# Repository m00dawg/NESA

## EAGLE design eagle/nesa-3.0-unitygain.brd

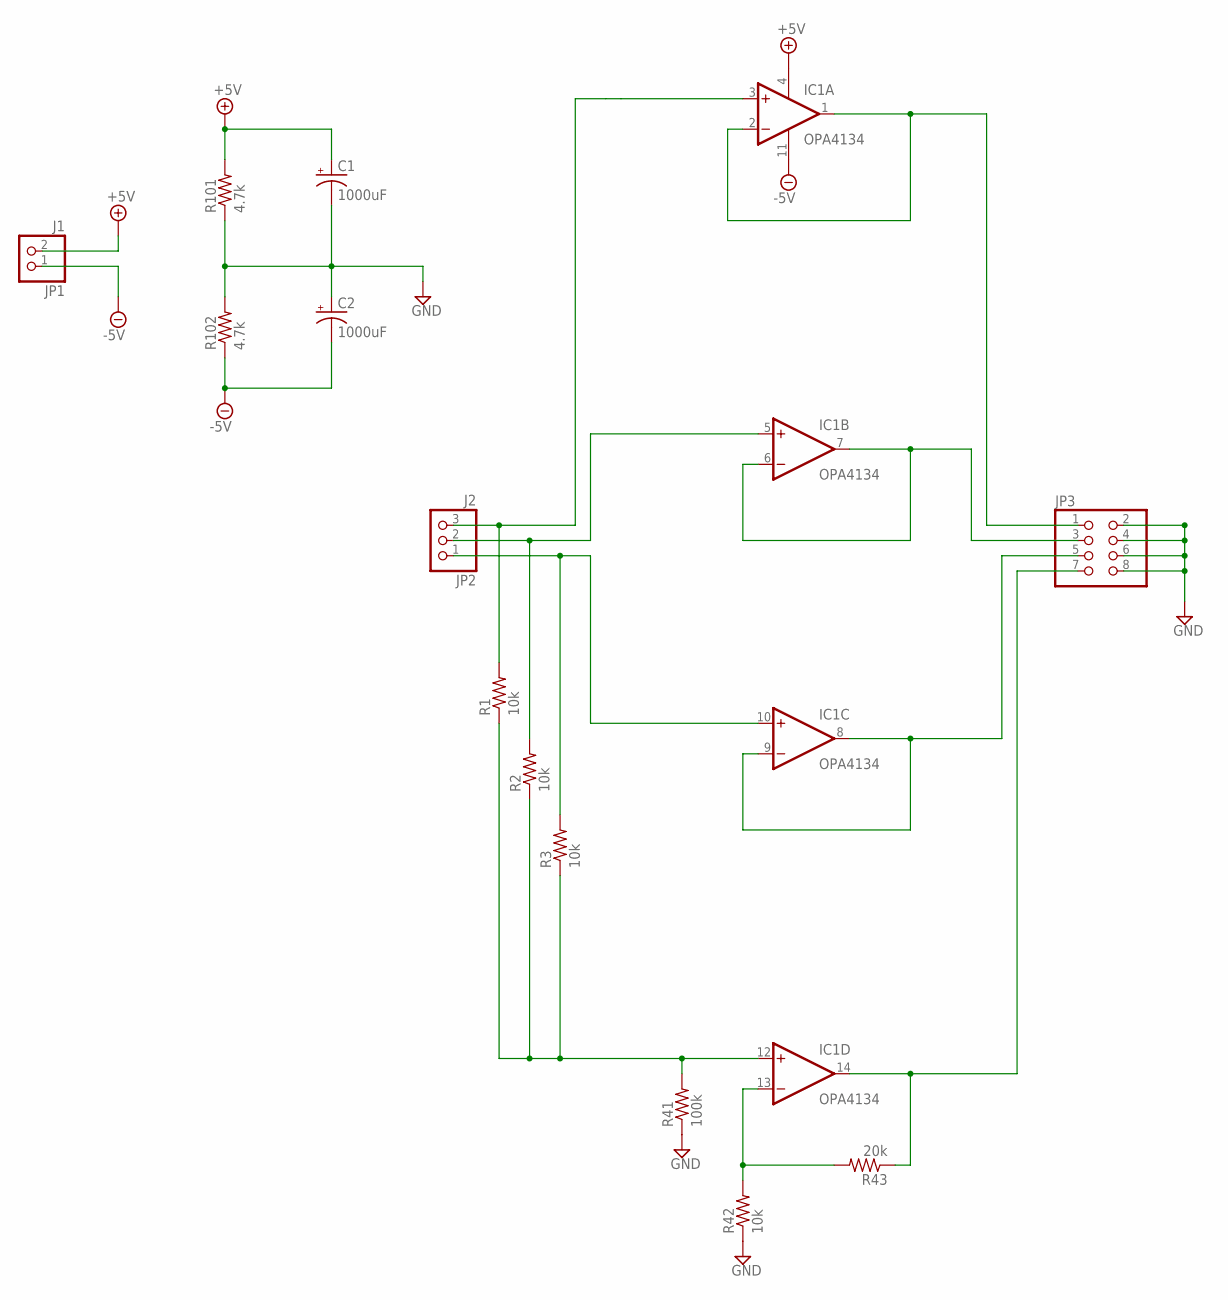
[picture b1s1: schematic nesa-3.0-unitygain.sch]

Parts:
C1, C2: 1000uF; E3,5-10
IC1: OPA4134; DIL14
JP1: J1; 1X02
JP2: J2; 1X03
JP3: PINHD-2X4; 2X04
R1, R2, R3, R42: 10k; 0204/7
R41: 100k; 0204/7
R43: 20k; 0204/7
R101, R102: 4.7k; 0204/7

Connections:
+5V: C1.+, IC1.4 (V+), JP1.2, R101.2
-5V: C2.-, IC1.11 (V-), JP1.1, R102.1
GND: C1.-, C2.+, JP3.2, JP3.4, JP3.6, JP3.8, R41.1, R42.1, R101.1, R102.2
unnamed: IC1.3 (+IN), JP2.3, R1.2
unnamed: IC1.1 (OUT), IC1.2 (-IN), JP3.1
unnamed: IC1.6 (-IN), IC1.7 (OUT), JP3.3
unnamed: IC1.10 (+IN), JP2.1, R3.2
unnamed: IC1.8 (OUT), IC1.9 (-IN), JP3.5
unnamed: IC1.5 (+IN), JP2.2, R2.2
unnamed: IC1.13 (-IN), R42.2, R43.2
unnamed: IC1.14 (OUT), JP3.7, R43.1
unnamed: IC1.12 (+IN), R1.1, R2.1, R3.1, R41.2

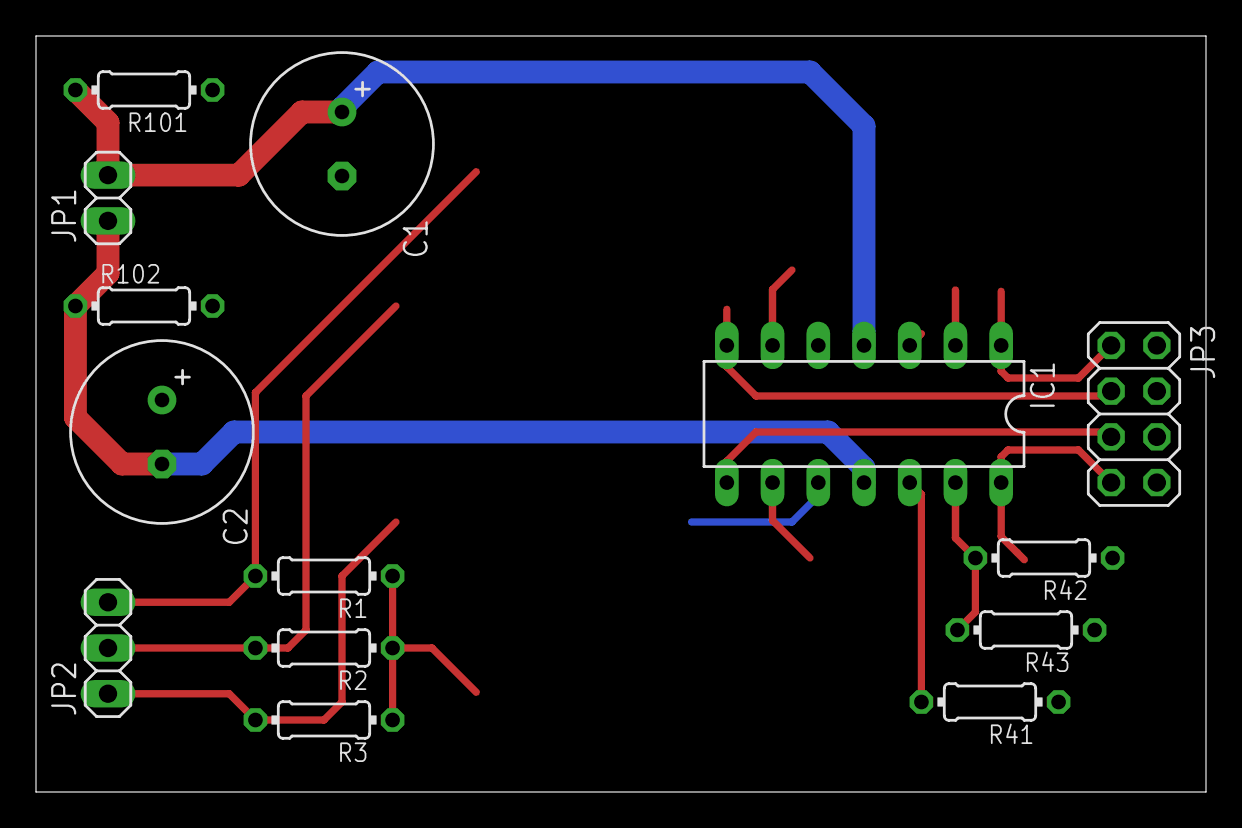
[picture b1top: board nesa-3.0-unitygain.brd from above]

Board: 2 copper layers, 65.0 x 42.0 mm, 14 parts (0 on the bottom side), 12 nets.

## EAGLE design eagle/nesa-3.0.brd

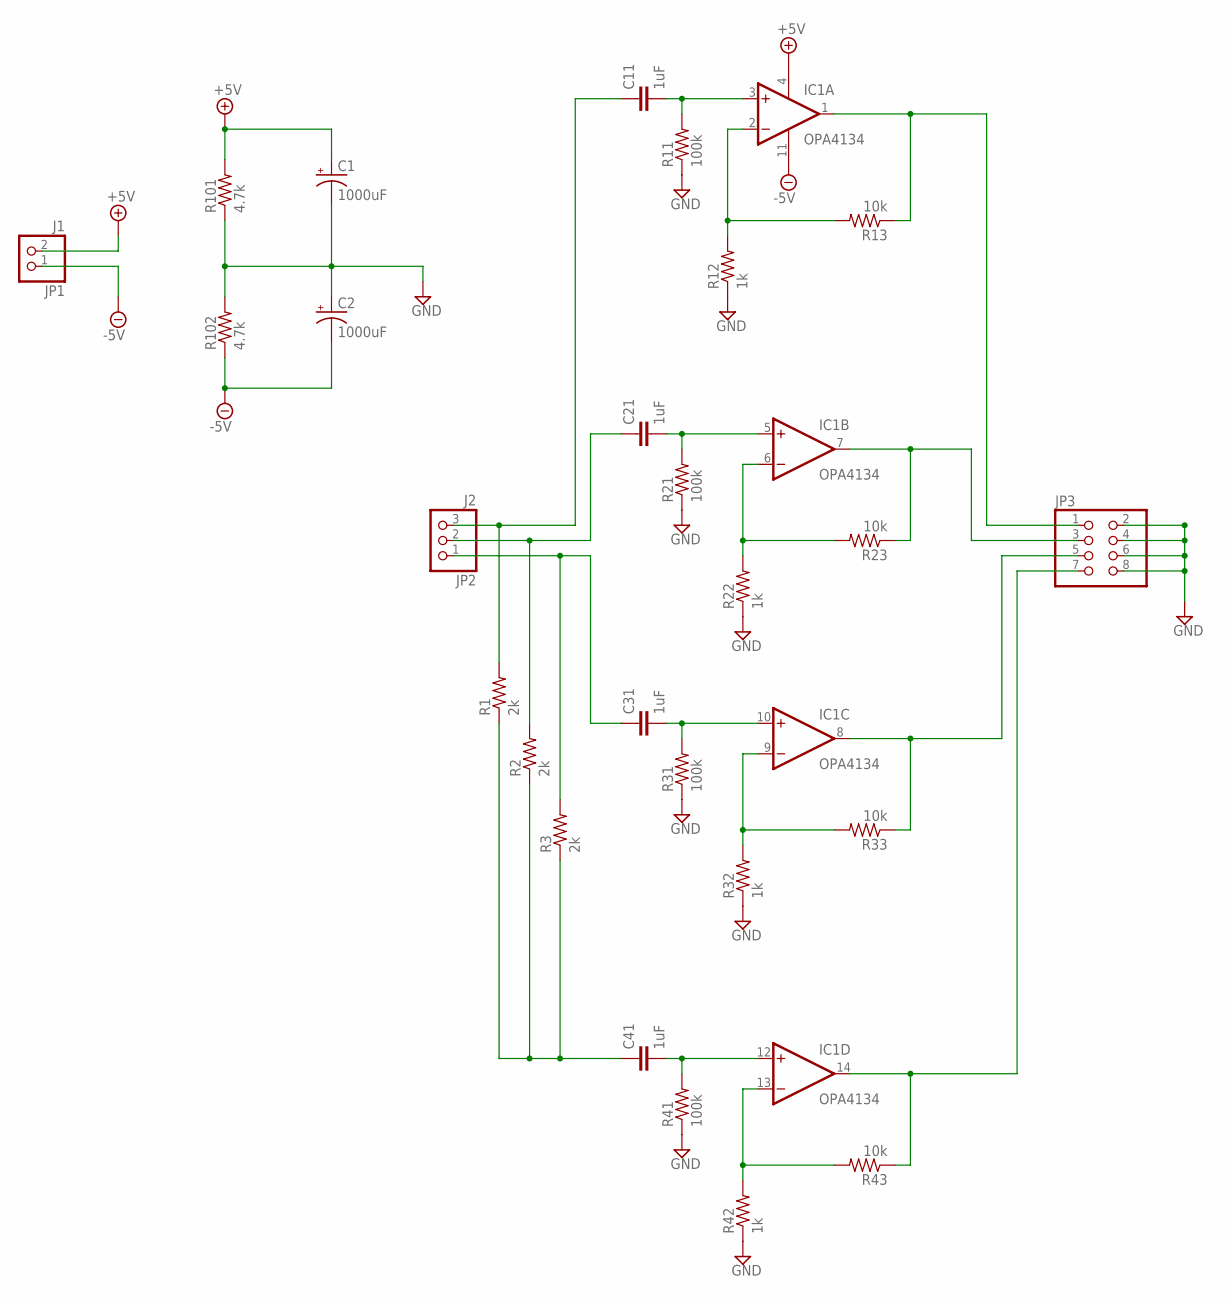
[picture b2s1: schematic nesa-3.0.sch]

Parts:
C1, C2: 1000uF; E3,5-10
C11, C21, C31, C41: 1uF; C5B7.2
IC1: OPA4134; DIL14
JP1: J1; 1X02
JP2: J2; 1X03
JP3: PINHD-2X4; 2X04
R1, R2, R3: 2k; 0204/7
R11, R21, R31, R41: 100k; 0204/7
R12, R22, R32, R42: 1k; 0204/7
R13, R23, R33, R43: 10k; 0204/7
R101, R102: 4.7k; 0204/7

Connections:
+5V: C1.+, IC1.4 (V+), JP1.2, R101.2
-5V: C2.-, IC1.11 (V-), JP1.1, R102.1
GND: C1.-, C2.+, JP3.2, JP3.4, JP3.6, JP3.8, R11.1, R12.1, R21.1, R22.1, R31.1, R32.1, R41.1, R42.1, R101.1, R102.2
unnamed: C11.1, JP2.3, R1.2
unnamed: IC1.2 (-IN), R12.2, R13.2
unnamed: C11.2, IC1.3 (+IN), R11.2
unnamed: IC1.1 (OUT), JP3.1, R13.1
unnamed: C21.2, IC1.5 (+IN), R21.2
unnamed: IC1.6 (-IN), R22.2, R23.2
unnamed: C31.2, IC1.10 (+IN), R31.2
unnamed: IC1.9 (-IN), R32.2, R33.2
unnamed: IC1.8 (OUT), JP3.5, R33.1
unnamed: C21.1, JP2.2, R2.2
unnamed: C31.1, JP2.1, R3.2
unnamed: C41.2, IC1.12 (+IN), R41.2
unnamed: IC1.7 (OUT), JP3.3, R23.1
unnamed: IC1.13 (-IN), R42.2, R43.2
unnamed: IC1.14 (OUT), JP3.7, R43.1
unnamed: C41.1, R1.1, R2.1, R3.1

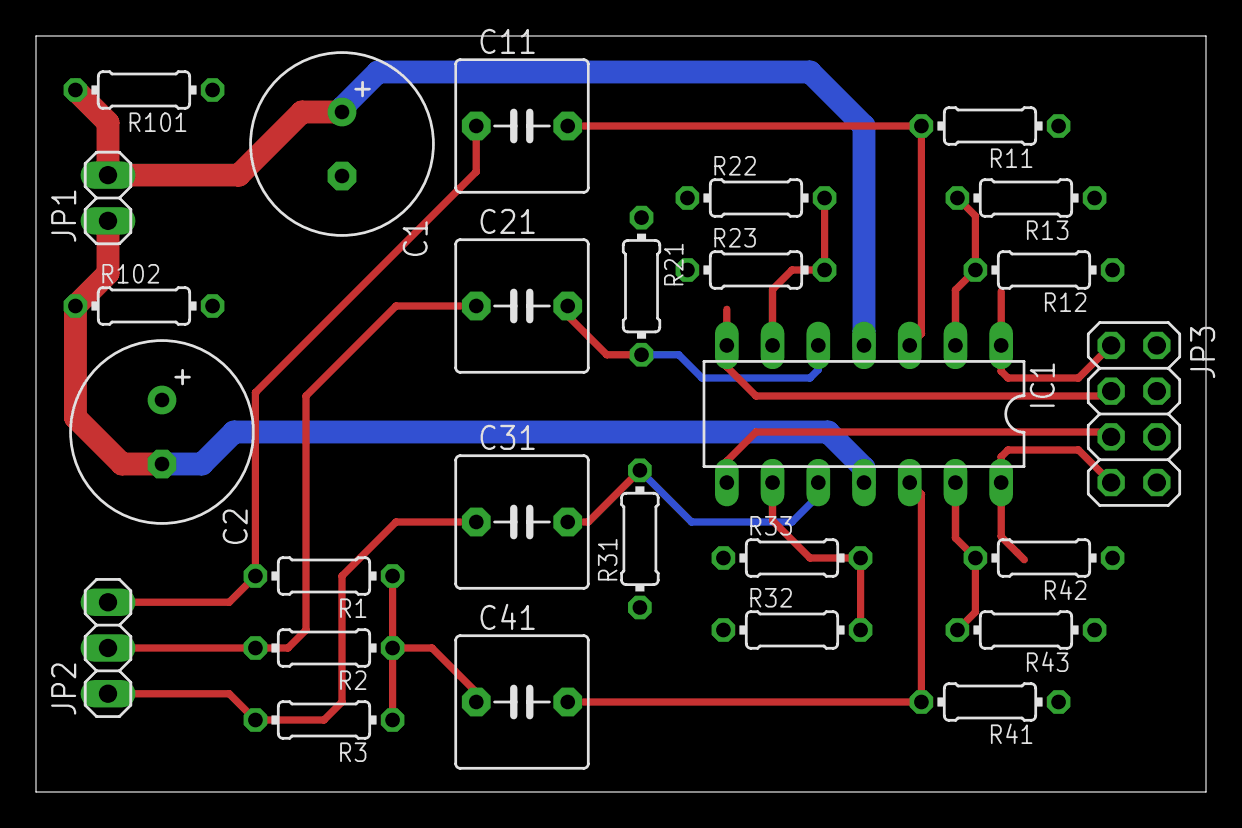
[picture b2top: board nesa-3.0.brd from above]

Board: 2 copper layers, 65.0 x 42.0 mm, 27 parts (0 on the bottom side), 19 nets.

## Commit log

2014-02-02 Initial Population using NESA 3.0 design
2014-02-02 Added an alterante schematic based on unity gain buffer
2014-02-02 Some minor changes to unitygain schematics
    Don't use these schematics yet :)
